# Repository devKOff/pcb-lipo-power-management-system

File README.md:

<div align="center">

# Project 2 — Power Management System

**A compact, integrated PCB for Li-Po battery charging, protection, and switch-selectable 5 V / 12 V output.**

Combines a TP4056 Li-Po charging stage, DW01A/FS8205A battery protection, and an MT3608 boost
converter on a single two-layer board — designed for portable electronics, IoT nodes,
Arduino-based projects, and lightweight UAV subsystems.

</div>

---

## Table of Contents

- [Overview](#overview)
- [3D Board Renders](#3d-board-renders)
- [Schematic](#schematic)
- [PCB Layer Breakdown](#pcb-layer-breakdown)
- [Bill of Materials & Manufacturing Files](#bill-of-materials--manufacturing-files)
- [Repository Structure](#repository-structure)
- [Getting Started](#getting-started)
- [License](#license)

---

## Overview

| | |
|---|---|
| **Board name** | Project 2 — Power Management System |
| **Function** | Li-Po charging + protection + selectable 5 V/12 V boost output |
| **Charging IC** | TP4056 (USB Type-C input, CC/CV charging) |
| **Protection ICs** | DW01A + FS8205A (overcharge / over-discharge / overcurrent) |
| **Boost converter** | MT3608 (switch-selectable ≈5 V / ≈12 V output) |
| **Layers** | 2-layer PCB |
| **EDA tool** | KiCad v10 |

---

## 3D Board Renders

<div align="center">

<table>
  <tr>
    <td align="center"><strong>Isometric View</strong></td>
    <td align="center"><strong>Top View</strong></td>
    <td align="center"><strong>Bottom View</strong></td>
  </tr>
  <tr>
    <td></td>
    <td></td>
    <td></td>
  </tr>
</table>

</div>

---

## Schematic

Full schematic of the charging, protection, and boost-conversion circuitry:

<div align="center">
  
</div>

> If the vector render above does not display (GitHub occasionally sandboxes inline SVG),
> open it directly: [`docs/images/schematics/project2.svg`](docs/images/schematics/project2.svg).
> A PNG fallback may also be available at `docs/images/schematics/project2.png`.

---

## PCB Layer Breakdown

### Primary Layers

**Top Copper (F.Cu)** | **Bottom Copper (B.Cu)**
:---:|:---:
 | 

**Top Silkscreen (F.Silkscreen)** | **Bottom Silkscreen (B.Silkscreen)**
:---:|:---:
 | 

**Board Outline (Edge.Cuts)**
:---:

### Supplementary Layers

<details>
<summary><strong>All-Layers Overlay</strong> (click to expand)</summary>
<br>

</details>

<details>
<summary><strong>Solder Mask Layers — Top (F.Mask) &amp; Bottom (B.Mask)</strong> (click to expand)</summary>
<br>

**Top Solder Mask (F.Mask)** | **Bottom Solder Mask (B.Mask)**
:---:|:---:
 | 

</details>

---

## Bill of Materials & Manufacturing Files

| Deliverable | Description | Link |
|---|---|---|
| 📋 Bill of Materials | Full component list with references, values, and quantities | [`docs/power_management_system_bom.csv`](docs/power_management_system_bom.csv) |
| 🏭 Gerber Files | Fabrication-ready Gerber package for PCB manufacturing | [`gerbers/`](gerbers/) |
| 🧩 STEP 3D CAD File | Mechanical 3D model for enclosure/assembly integration | [`step/`](step/) |
| 🗂️ KiCad Project | Top-level KiCad project file | [`project2.kicad_pro`](project2.kicad_pro) |
| 🔲 KiCad PCB Layout | Editable PCB layout file | [`project2.kicad_pcb`](project2.kicad_pcb) |
| ⚡ KiCad Schematic | Editable schematic source file | [`project2.kicad_sch`](project2.kicad_sch) |

> **Note:** If the BOM is provided as a spreadsheet instead of CSV, use
> [`docs/power_management_system_bom.xlsx`](docs/power_management_system_bom.xlsx).

---

## Repository Structure

```text
pcb-lipo-power-management-system/
├── docs/
│   ├── images/
│   │   ├── 3d_views/
│   │   │   ├── 3d_top.png
│   │   │   ├── 3d_iso.png
│   │   │   └── 3d_bottom.png
│   │   ├── schematics/
│   │   │   └── project2.svg
│   │   └── pcb_layers/
│   │       ├── pcb_All_layers.svg
│   │       ├── project2-F_Cu.svg
│   │       ├── project2-B_Cu.svg
│   │       ├── project2-F_Silkscreen.svg
│   │       ├── project2-B_Silkscreen.svg
│   │       ├── project2-F_Mask.svg
│   │       ├── project2-B_Mask.svg
│   │       └── project2-Edge_Cuts.svg
│   └── power_management_system_bom.csv
├── gerbers/
│   └── (fabrication Gerber + drill files)
├── step/
│   └── (STEP 3D CAD export)
├── assets/
│   └── datasheets/
│       └── (component datasheets: TP4056, MT3608, DW01A, FS8205A, etc.)
├── .history/
│   └── (local edit history / backups, excluded from releases)
├── .gitignore
├── DRC.rpt
├── report.txt
├── project2.kicad_pro
├── project2.kicad_pcb
├── project2.kicad_prl
├── project2.kicad_sch
├── LICENSE
└── README.md
```

> **Note:** `.history/`, `DRC.rpt`, `report.txt`, and `temp-freerouting.dsn` are local
> KiCad/tooling artifacts. Consider adding them to `.gitignore` if they don't need to be
> version-controlled — they're listed here only for completeness.

---

## Getting Started

1. **Clone the repository**
   ```bash
   git clone https://github.com/devKOff/pcb-lipo-power-management-system.git
   cd pcb-lipo-power-management-system
   ```
2. **Open in KiCad v10**
   Open [`project2.kicad_pro`](project2.kicad_pro) in KiCad to view or edit the schematic and PCB layout.
3. **Manufacture the board**
   Send the contents of [`gerbers/`](gerbers/) directly to your PCB fabricator, and reference
   [`docs/power_management_system_bom.csv`](docs/power_management_system_bom.csv) for assembly.
4. **Mechanical integration**
   Import the STEP file from [`step/`](step/) into your CAD tool of choice for enclosure or
   assembly design.

---

## License

This project is released under the terms of the [MIT License](LICENSE). Hardware design files
are shared in the spirit of open source hardware — see the OSHW badge above.

> **Note:** No `LICENSE` file currently exists in this repository. Add one (e.g. via GitHub's
> *Add file → Create new file → LICENSE* flow, which offers an MIT template) so the badge and
> link above resolve correctly — see Step 6 in the upload guide below.

<div align="center">

*Maintained as part of the Project 2 — Power Management System hardware design effort.*

</div>

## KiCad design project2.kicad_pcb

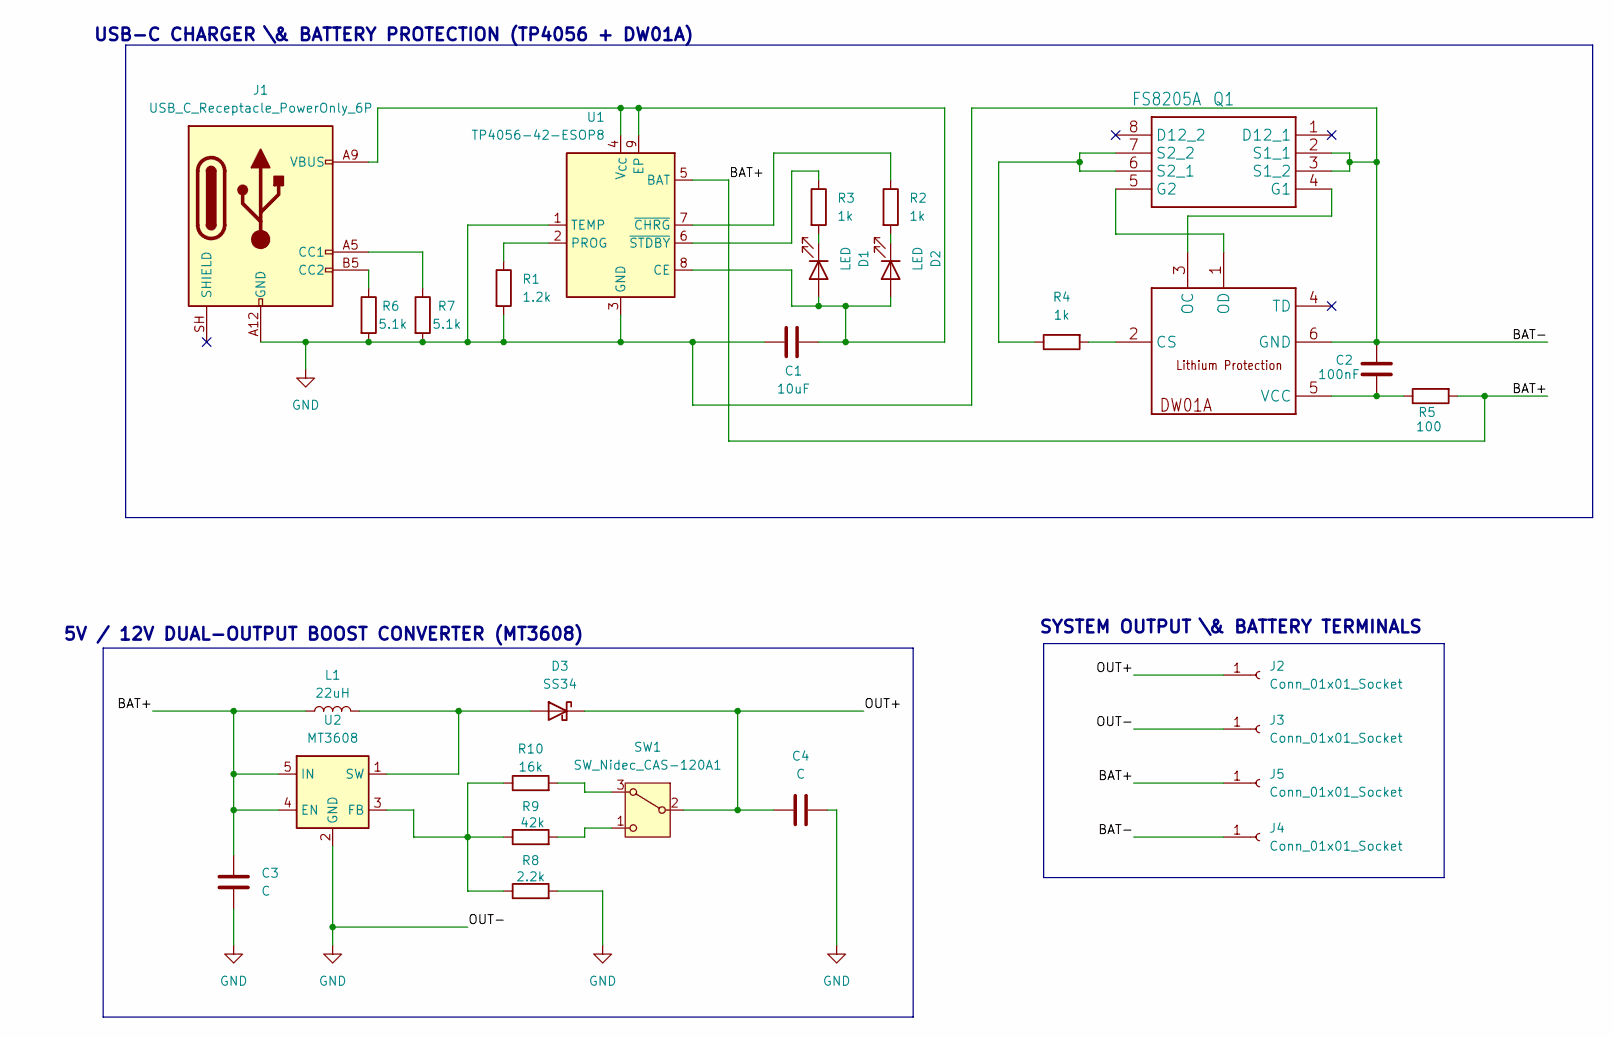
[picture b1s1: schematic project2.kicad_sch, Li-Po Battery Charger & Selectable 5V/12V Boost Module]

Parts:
C1: 10uF; C_0805_2012Metric
C2: 100nF; C_0805_2012Metric
C3, C4: C; D_SMA
D1, D2: LED; LED_0805_2012Metric
D3: SS34; D_SMA
J1: USB_C_Receptacle_PowerOnly_6P; USB_C_Receptacle_GCT_USB4125-xx-x_6P_TopMnt_Horizontal
J2, J3, J4, J5: Conn_01x01_Socket; SolderWirePad_1x01_SMD_1.5x3mm
L1: 22uH; L_7.3x7.3_H4.5
Q1: FS8205A; SOP65P640X120-8N; Manufacturer_Part_Number FS8205A
Q2: DW01A; SOT-23-6
R1: 1.2k; R_0805_2012Metric
R2, R3, R4: 1k; R_0805_2012Metric
R5: 100; R_0805_2012Metric
R6, R7: 5.1k; R_0805_2012Metric
R8: 2.2k; R_0805_2012Metric
R9: 42k; R_0805_2012Metric
R10: 16k; R_0805_2012Metric
SW1: SW_Nidec_CAS-120A1; Nidec_Copal_CAS-120A
U1: TP4056-42-ESOP8; SOIC-8-1EP_3.9x4.9mm_P1.27mm_EP2.41x3.3mm_ThermalVias
U2: MT3608; SOT-23-6

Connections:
/BAT+: C3.1, J5.1 (Pin_1_1), L1.1, R5.2, U1.5 (BAT), U2.4 (EN), U2.5 (IN)
/OUT+: C4.2, D3.1 (K), J2.1 (Pin_1_1), SW1.2 (B)
GND: C1.1, C2.1, C3.2, C4.1, J1.A12 (GND), J1.B12 (GND), J3.1 (Pin_1_1), J4.1 (Pin_1_1), Q1.2 (S1_1), Q1.3 (S1_2), Q2.6 (GND), R1.2, R6.2, R7.2, R8.2, U1.1 (TEMP), U1.3 (GND), U2.2 (GND)
unnamed: C1.2, D1.2 (A), D2.2 (A), J1.A9 (VBUS), J1.B9 (VBUS), U1.4 (V_{CC}), U1.8 (CE), U1.9 (EP)
unnamed: D1.1 (K), R3.2
unnamed: D2.1 (K), R2.2
unnamed: D3.2 (A), L1.2, U2.1 (SW)
unnamed: J1.A5 (CC1), R7.1
unnamed: J1.B5 (CC2), R6.1
unnamed: Q1.4 (G1), Q2.3 (OC)
unnamed: Q1.5 (G2), Q2.1 (OD)
unnamed: Q1.6 (S2_1), Q1.7 (S2_2), R4.1
unnamed: Q2.2 (CS), R4.2
unnamed: C2.2, Q2.5 (VCC), R5.1
unnamed: R10.2, SW1.3 (A)
unnamed: R9.2, SW1.1 (C)
unnamed: R1.1, U1.2 (PROG)
unnamed: R2.1, U1.7 (~CHRG)
unnamed: R3.1, U1.6 (~STDBY)
unnamed: R8.1, R9.1, R10.1, U2.3 (FB)

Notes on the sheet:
USB-C CHARGER \& BATTERY PROTECTION (TP4056 + DW01A)
5V / 12V DUAL-OUTPUT BOOST CONVERTER (MT3608)
SYSTEM OUTPUT \& BATTERY TERMINALS

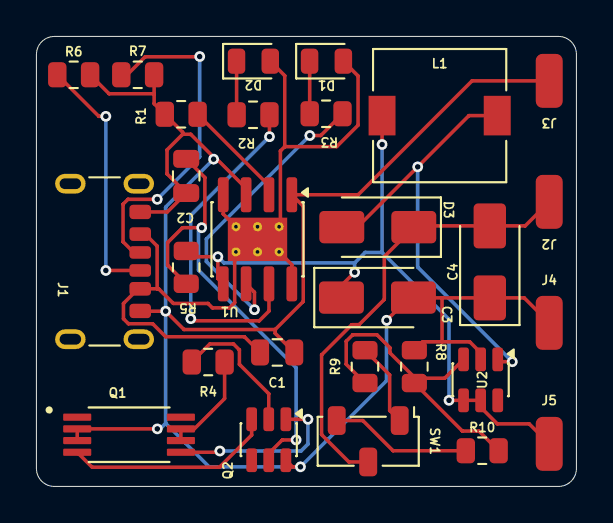
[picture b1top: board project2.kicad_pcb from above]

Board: 2 copper layers, 30.0 x 25.0 mm, 28 parts (0 on the bottom side), 20 nets.

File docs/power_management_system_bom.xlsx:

Bill of Materials (BOM) — Power Management System
Project: Integrated PCB Li-Po Charger & Selectable 5V/12V Boost Module | Sheet: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
Item # | Ref Des | Qty | Value / Part | Category / Function | KiCad Symbol Library | Footprint / Package | Part Number / LCSC Ref | Description
Active Integrated Circuits & Semiconductors
1 | U1 | 1 | TP4056-42-ESOP8 | Power Management IC | Power_Management | Package_SO:SOP-8-PP_3.9x4.9mm_P1.27mm | TP4056 / C16581 | 1A Standalone Linear Li-Ion Battery Charger
2 | U2 | 1 | MT3608 | DC-DC Boost Converter | Power_Switching | Package_TO_SOT_SMD:SOT-23-6 | MT3608 / C84817 | 1.2MHz, 2A High-Efficiency Step-Up Converter
3 | U3 | 1 | DW01A | Battery Protection IC | Battery_Management | Package_TO_SOT_SMD:SOT-23-6 | DW01A / C14211 | One-Cell Li-Ion/Li-Po Battery Protection Controller
4 | Q1 | 1 | FS8205A | Protection MOSFET | Transistor_FET | Package_SO:TSSOP-8_4.4x3mm_P0.65mm | FS8205A / C16130 | Dual N-Channel Common-Drain MOSFET Switch
5 | D3 | 1 | SS34 | Schottky Diode | Diode | Diode_SMD:D_SMA | SS34 / C1591 | 3A / 40V Surface Mount Schottky Barrier Diode
6 | D1, D2 | 2 | LED (Red/Green) | Status Indicators | Device | LED_SMD:LED_0805_2012Metric | Generic 0805 LED | Surface Mount Status Indicators (CHRG / STDBY)
Resistors (SMD 0805)
7 | R1 | 1 | 1.2kΩ | Resistor | Device | Resistor_SMD:R_0805_2012Metric | 0805W8F1201T5E | Sets TP4056 charge current to 1A (PROG)
8 | R2, R3 | 2 | 1kΩ | Resistor | Device | Resistor_SMD:R_0805_2012Metric | 0805W8F1001T5E | LED Current Limiting Resistors
9 | R4 | 1 | 1kΩ | Resistor | Device | Resistor_SMD:R_0805_2012Metric | 0805W8F1001T5E | DW01A Overcurrent Current-Sense Resistor
10 | R5 | 1 | 100Ω | Resistor | Device | Resistor_SMD:R_0805_2012Metric | 0805W8F1000T5E | DW01A VCC Filtering Resistor
11 | R6, R7 | 2 | 5.1kΩ | Resistor | Device | Resistor_SMD:R_0805_2012Metric | 0805W8F5101T5E | USB Type-C CC1/CC2 Pull-down Resistors
12 | R8 | 1 | 2.2kΩ | Resistor | Device | Resistor_SMD:R_0805_2012Metric | 0805W8F2201T5E | MT3608 Feedback Divider Ground Resistor
13 | R9 | 1 | 42kΩ | Resistor | Device | Resistor_SMD:R_0805_2012Metric | 0805W8F4202T5E | MT3608 Feedback Resistor (Selects ~12V Output)
14 | R10 | 1 | 16kΩ | Resistor | Device | Resistor_SMD:R_0805_2012Metric | 0805W8F1602T5E | MT3608 Feedback Resistor (Selects ~5V Output)
Capacitors & Power Passives
15 | C1 | 1 | 10uF | Ceramic Capacitor | Device | Capacitor_SMD:C_0805_2012Metric | CL21A106KOQNNNE | TP4056 Input/Output Decoupling Capacitor
16 | C2 | 1 | 100nF | Ceramic Capacitor | Device | Capacitor_SMD:C_0603_1608Metric | CL10B104KO8NNNC | DW01A VCC Power Decoupling Capacitor
17 | C3, C4 | 2 | 10uF | Ceramic Capacitor | Device | Capacitor_SMD:C_0805_2012Metric | CL21A106KOQNNNE | MT3608 Input & Output Filter Capacitors
18 | L1 | 1 | 22uH | Power Inductor | Device | Inductor_SMD:L_7.3x7.3_H4.5 | CDRH74T-220MC / C16822 | 22µH Shielded Power Inductor (Boost Converter)
Connectors & Switches
19 | J1 | 1 | USB_C_6P | USB Receptacle | Connector | Connector_USB:USB_C_Receptacle_6P | TYPE-C-31-M-12 / C165948 | USB Type-C 6-Pin Power Input Jack
20 | SW1 | 1 | SW_SPDT | Slide Switch | Switch | Button_Switch_SMD:SW_SPDT_PCM12 | CAS-120A1 / SK-12D07 | SPDT Switch for 5V / 12V Voltage Rail Selection
21 | J2, J3 | 2 | 1-Pin Header | Output Terminal | Connector | Connector_PinHeader_2.54mm:1x01 | Generic 2.54mm Header | System Output Pins (OUT+, OUT-)
22 | J4, J5 | 2 | 1-Pin Header | Battery Terminal | Connector | Connector_PinHeader_2.54mm:1x01 | Generic 2.54mm Header | Li-Po Battery Connector Pins (BAT+, BAT-)
Total Components:

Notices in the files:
README.md:
License: MIT
